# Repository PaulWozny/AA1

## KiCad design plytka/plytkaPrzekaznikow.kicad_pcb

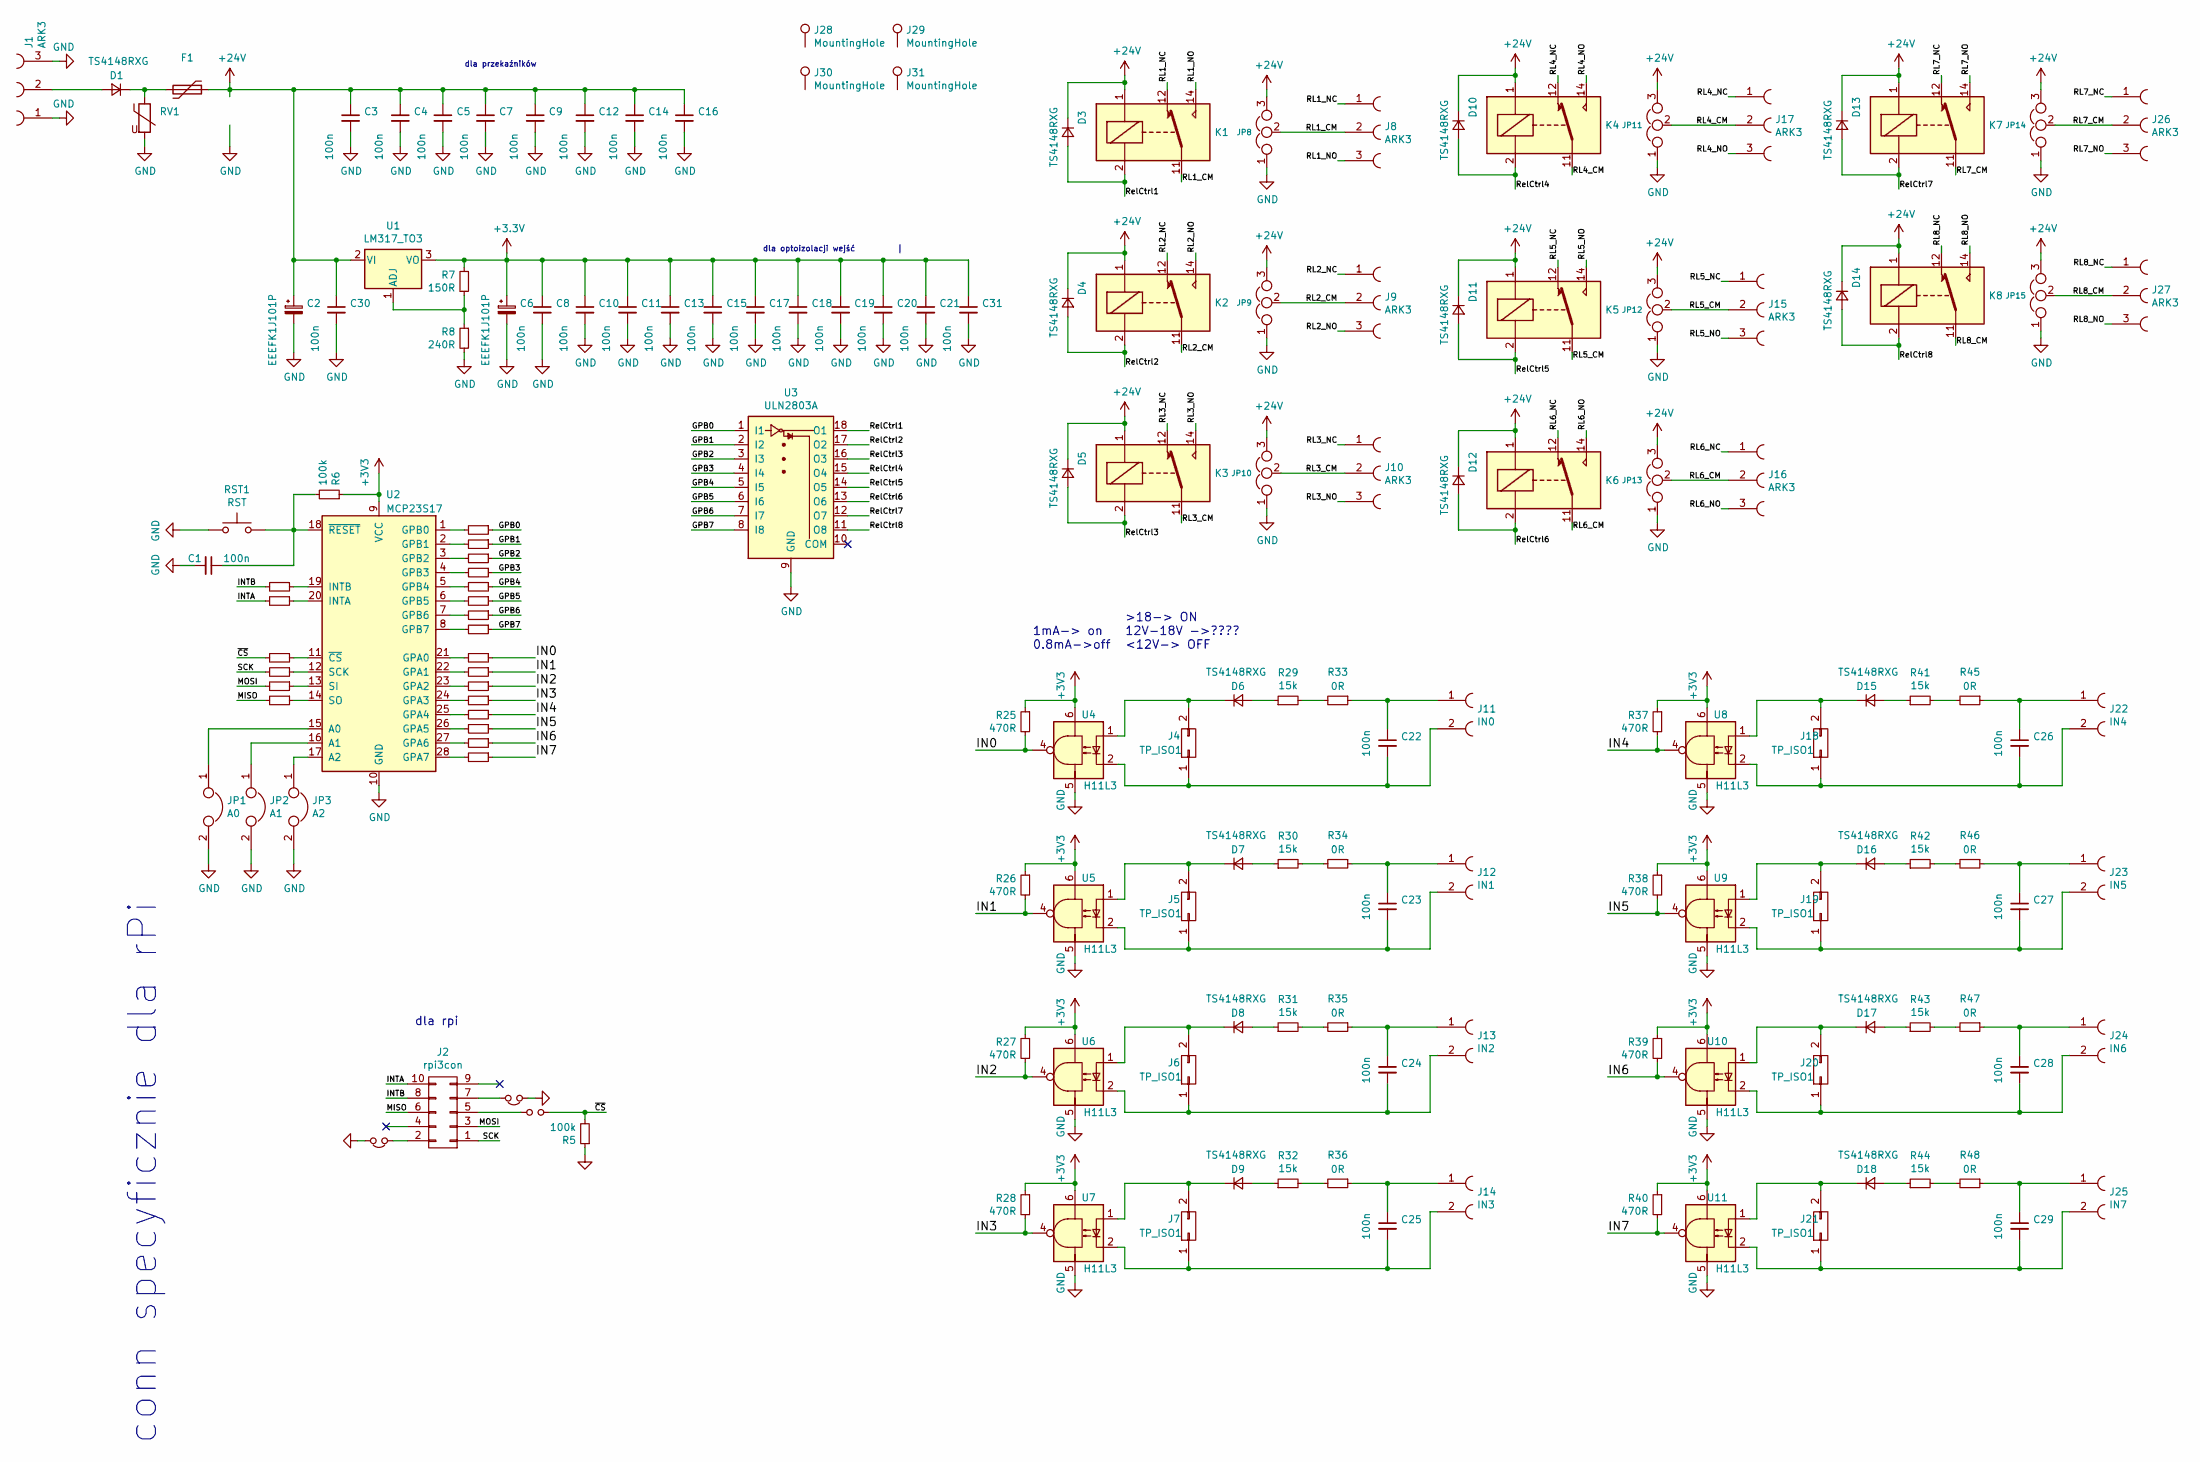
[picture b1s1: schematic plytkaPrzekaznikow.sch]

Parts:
C1, C3, C4, C5, C7, C8, C9, C10, C11, C12, C13, C14, C15, C16, C17, C18, C19, C20, C21, C22, C23, C24, C25, C26, C27, C28, C29, C30, C31: 100n; C_0805
C2, C6: EEEFK1J101P; c_elec_10x10.5
D1, D3, D4, D5, D6, D7, D8, D9, D10, D11, D12, D13, D14, D15, D16, D17, D18: TS4148RXG; R_1206
F1: wiringPiNodeStruct; R_1210
J1, J8, J9, J10, J15, J16, J17, J26, J27: ARK3; AK300-3
J2: rpi3con; IDC_Header_Straight_10pins
J4, J5, J6, J7, J18, J19, J20, J21: TP_ISO1; Pin_Header_Straight_2x01_Pitch2.54mm
J11: IN0; AK300-2
J12: IN1; AK300-2
J13: IN2; AK300-2
J14: IN3; AK300-2
J22: IN4; AK300-2
J23: IN5; AK300-2
J24: IN6; AK300-2
J25: IN7; AK300-2
J28, J29, J30, J31: MountingHole; MountingHole_3.2mm_M3_ISO14580
JP1: A0; NetTie-I_Connected_SMD_SMALL
JP2: A1; NetTie-I_Connected_SMD_SMALL
JP3: A2; NetTie-I_Connected_SMD_SMALL
JP4: ~CSEN; R_0805
JP5, JP7: GND; NetTie-I_SMD_Small
JP8, JP9, JP10, JP11, JP12, JP13, JP14, JP15: Jumper_NC_Dual; NetTie-II_SMD_NC_BIG
K1, K2, K3, K4, K5, K6, K7, K8: RM50N3011851024; Relay_SANYOU_SRD_Series_Form_C
R1, R2, R3, R4, R9, R10, R11, R12, R13, R14, R15, R16, R17, R18, R19, R20, R21, R22, R23, R24, R49, R50: 470; R_0805
R5, R6: 100k; R_0805
R7: 150R; R_0805
R8: 240R; R_0805
R25, R26, R27, R28, R37, R38, R39, R40: 470R; R_0805
R29, R30, R31, R32, R41, R42, R43, R44: 15k; R_1206
R33, R34, R35, R36, R45, R46, R47, R48: 0R; R_1206
RST1: RST; SW_SPST_B3U-1000P
RV1: SR101K05D; Resistor_Horizontal_RM7mm
U1: LM317_TO3; TO-220_Neutral123_Vertical
U2: MCP23S17; DIP-28_W15.24mm_Socket
U3: ULN2803A; DIP-18_W7.62mm_Socket_LongPads
U4, U5, U6, U7, U8, U9, U10, U11: H11L3; DIP-6_W7.62mm_Socket

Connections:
+24V: C2.1, C3.1, C4.1, C5.1, C7.1, C9.1, C12.1, C14.1, C16.1, C30.1, D3.1 (K), D4.1 (K), D5.1 (K), D10.1 (K), D11.1 (K), D12.1 (K), D13.1 (K), D14.1 (K), F1.1, JP8.3, JP9.3, JP10.3, JP11.3, JP12.3, JP13.3, JP14.3, JP15.3, K1.1, K2.1, K3.1, K4.1, K5.1, K6.1, K7.1, K8.1, U1.2 (VI)
/GPB0: R9.1, U3.1 (I1)
/GPB1: R10.1, U3.2 (I2)
/GPB2: R11.1, U3.3 (I3)
/GPB3: R12.1, U3.4 (I4)
/GPB4: R13.1, U3.5 (I5)
/GPB5: R14.1, U3.6 (I6)
/GPB6: R15.1, U3.7 (I7)
/GPB7: R16.1, U3.8 (I8)
/IN0: R17.1, R25.2, U4.4
/IN1: R18.1, R26.2, U5.4
/IN2: R19.1, R27.2, U6.4
/IN3: R20.1, R28.2, U7.4
/IN4: R21.1, R37.2, U8.4
/IN5: R22.1, R38.2, U9.4
/IN6: R23.1, R39.2, U10.4
/IN7: R24.1, R40.2, U11.4
/INTA: J2.10, R50.2
/INTB: J2.8, R49.2
/MISO: J2.6, R4.2
/MOSI: J2.3, R3.2
/RL1_CM: J8.2, JP8.2, K1.11
/RL1_NC: J8.1, K1.12
/RL1_NO: J8.3, K1.14
/RL2_CM: J9.2, JP9.2, K2.11
/RL2_NC: J9.1, K2.12
/RL2_NO: J9.3, K2.14
/RL3_CM: J10.2, JP10.2, K3.11
/RL3_NC: J10.1, K3.12
/RL3_NO: J10.3, K3.14
/RL4_CM: J17.2, JP11.2, K4.11
/RL4_NC: J17.1, K4.12
/RL4_NO: J17.3, K4.14
/RL5_CM: J15.2, JP12.2, K5.11
/RL5_NC: J15.1, K5.12
/RL5_NO: J15.3, K5.14
/RL6_CM: J16.2, JP13.2, K6.11
/RL6_NC: J16.1, K6.12
/RL6_NO: J16.3, K6.14
/RL7_CM: J26.2, JP14.2, K7.11
/RL7_NC: J26.1, K7.12
/RL7_NO: J26.3, K7.14
/RL8_CM: J27.2, JP15.2, K8.11
/RL8_NC: J27.1, K8.12
/RL8_NO: J27.3, K8.14
/RelCtrl1: D3.2 (A), K1.2, U3.18 (O1)
/RelCtrl2: D4.2 (A), K2.2, U3.17 (O2)
/RelCtrl3: D5.2 (A), K3.2, U3.16 (O3)
/RelCtrl4: D10.2 (A), K4.2, U3.15 (O4)
/RelCtrl5: D11.2 (A), K5.2, U3.14 (O5)
/RelCtrl6: D12.2 (A), K6.2, U3.13 (O6)
/RelCtrl7: D13.2 (A), K7.2, U3.12 (O7)
/RelCtrl8: D14.2 (A), K8.2, U3.11 (O8)
/SCK: J2.1, R2.2
/~CS: JP4.1, R1.2, R5.2
GND: C1.2, C2.2, C3.2, C4.2, C5.2, C6.2, C7.2, C8.2, C9.2, C10.2, C11.2, C12.2, C13.2, C14.2, C15.2, C16.2, C17.2, C18.2, C19.2, C20.2, C21.2, C30.2, C31.2, J1.1, J1.3, JP1.2, JP2.2, JP3.2, JP5.1, JP7.2, JP8.1, JP9.1, JP10.1, JP11.1, JP12.1, JP13.1, JP14.1, JP15.1, R5.1, R8.2, RST1.1, RV1.2, U2.10 (GND), U3.9 (GND), U4.5, U5.5, U6.5, U7.5, U8.5, U9.5, U10.5, U11.5
unnamed: C1.1, R6.2, RST1.2, U2.18 (~RESET)
unnamed: C22.1, J11.1, R33.1
unnamed: C22.2, J4.1, J11.2, U4.2
unnamed: C23.1, J12.1, R34.1
unnamed: C23.2, J5.1, J12.2, U5.2
unnamed: C24.1, J13.1, R35.1
unnamed: C24.2, J6.1, J13.2, U6.2
unnamed: C25.1, J14.1, R36.1
unnamed: C25.2, J7.1, J14.2, U7.2
unnamed: C26.1, J22.1, R45.1
unnamed: C26.2, J18.1, J22.2, U8.2
unnamed: C27.1, J23.1, R46.1
unnamed: C27.2, J19.1, J23.2, U9.2
unnamed: C28.1, J24.1, R47.1
unnamed: C28.2, J20.1, J24.2, U10.2
unnamed: C29.1, J25.1, R48.1
unnamed: C29.2, J21.1, J25.2, U11.2
unnamed: D1.1 (K), F1.2, RV1.1
unnamed: D1.2 (A), J1.2
unnamed: D6.1 (K), J4.2, U4.1
unnamed: D6.2 (A), R29.1
unnamed: D7.1 (K), J5.2, U5.1
unnamed: D7.2 (A), R30.1
unnamed: D8.1 (K), J6.2, U6.1
unnamed: D8.2 (A), R31.1
unnamed: D9.1 (K), J7.2, U7.1
unnamed: D9.2 (A), R32.1
unnamed: D15.1 (K), J18.2, U8.1
unnamed: D15.2 (A), R41.1
unnamed: D16.1 (K), J19.2, U9.1
unnamed: D16.2 (A), R42.1
unnamed: D17.1 (K), J20.2, U10.1
unnamed: D17.2 (A), R43.1
unnamed: D18.1 (K), J21.2, U11.1
unnamed: D18.2 (A), R44.1
unnamed: J2.2, JP5.2
unnamed: J2.5, JP4.2
unnamed: J2.7, JP7.1
unnamed: JP1.1, U2.15 (A0)
unnamed: JP2.1, U2.16 (A1)
unnamed: JP3.1, U2.17 (A2)
unnamed: R1.1, U2.11 (~CS)
unnamed: R2.1, U2.12 (SCK)
unnamed: R3.1, U2.13 (SI)
unnamed: R4.1, U2.14 (SO)
unnamed: R7.2, R8.1, U1.1 (ADJ)
unnamed: R9.2, U2.1 (GPB0)
unnamed: R10.2, U2.2 (GPB1)
unnamed: R11.2, U2.3 (GPB2)
unnamed: R12.2, U2.4 (GPB3)
unnamed: R13.2, U2.5 (GPB4)
unnamed: R14.2, U2.6 (GPB5)
unnamed: R15.2, U2.7 (GPB6)
unnamed: R16.2, U2.8 (GPB7)
unnamed: R17.2, U2.21 (GPA0)
unnamed: R18.2, U2.22 (GPA1)
unnamed: R19.2, U2.23 (GPA2)
unnamed: R20.2, U2.24 (GPA3)
unnamed: R21.2, U2.25 (GPA4)
unnamed: R22.2, U2.26 (GPA5)
unnamed: R23.2, U2.27 (GPA6)
unnamed: R24.2, U2.28 (GPA7)
unnamed: R29.2, R33.2
unnamed: R30.2, R34.2
unnamed: R31.2, R35.2
unnamed: R32.2, R36.2
unnamed: R41.2, R45.2
unnamed: R42.2, R46.2
unnamed: R43.2, R47.2
unnamed: R44.2, R48.2
unnamed: R49.1, U2.19 (INTB)
unnamed: R50.1, U2.20 (INTA)

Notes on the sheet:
conn specyficznie dla rPi
dla rpi
1mA-> on 0.8mA->off
>18-> ON 12V-18V ->???? <12V-> OFF
dla przekaźników
dla optoizolacji wejść |

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
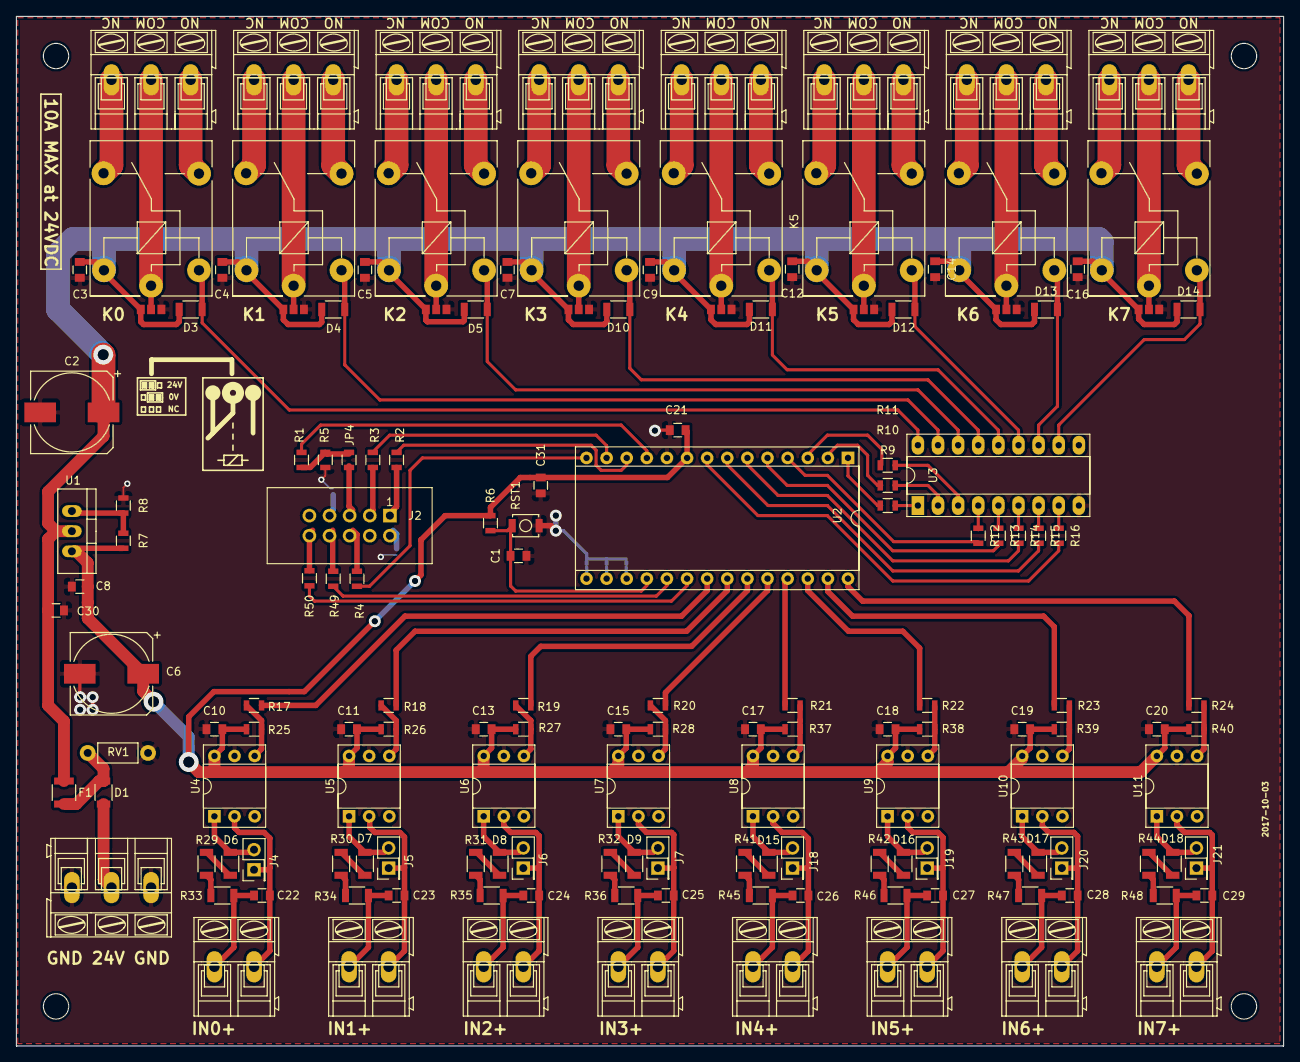
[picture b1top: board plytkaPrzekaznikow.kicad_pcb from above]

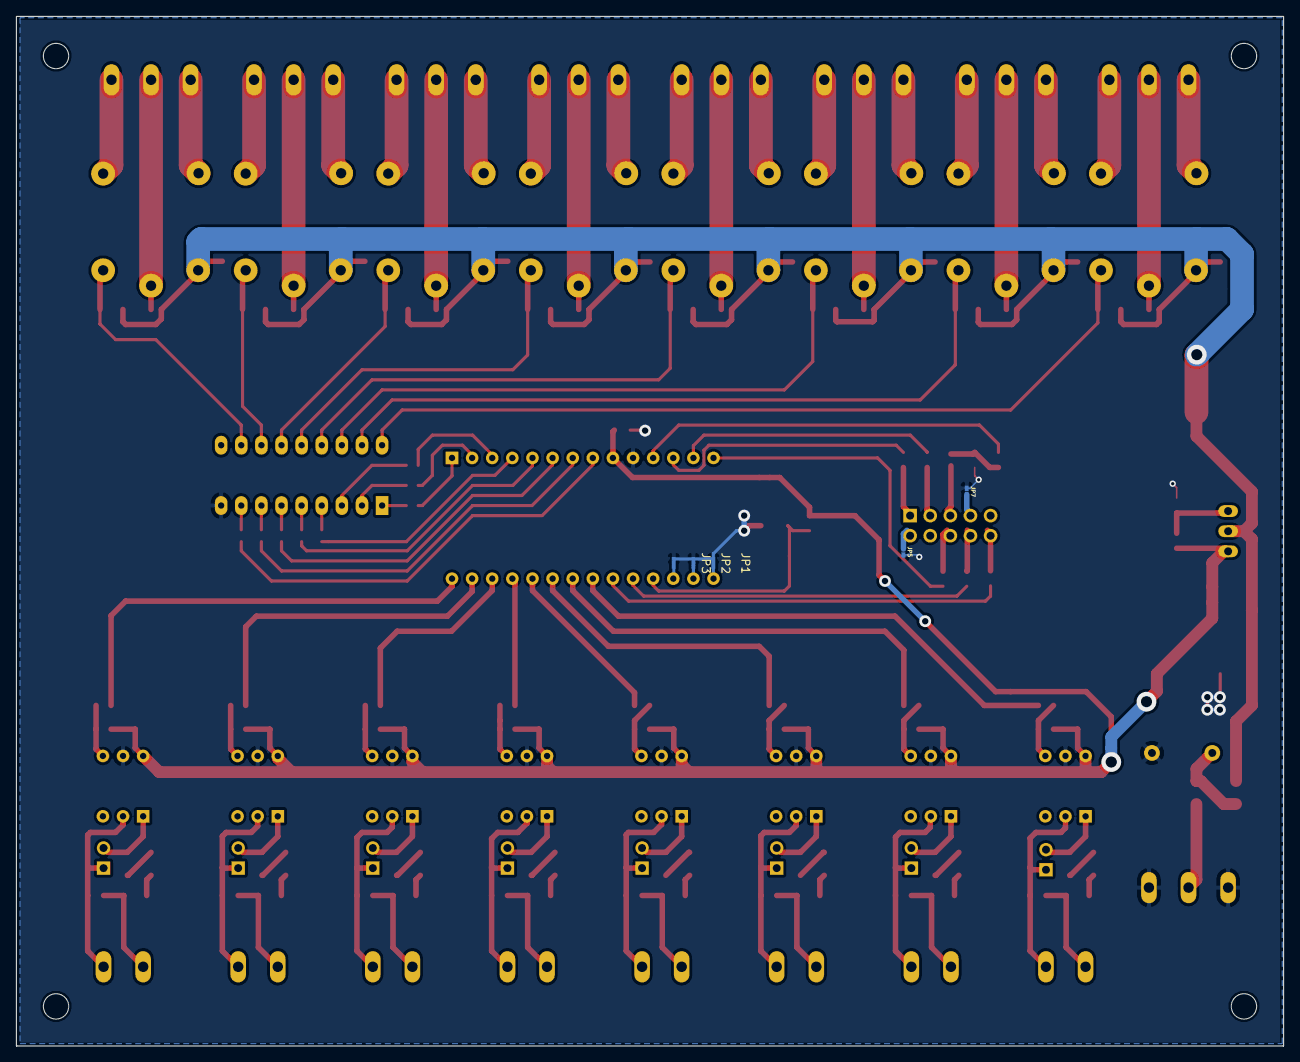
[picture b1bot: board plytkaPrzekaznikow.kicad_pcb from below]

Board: 2 copper layers, 160.0 x 130.0 mm, 164 parts (5 on the bottom side), 129 nets.

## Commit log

2017-11-20 hehe xd teraz mamy wszystkie softy
2017-11-22 dzisaj dodano buttonsy
